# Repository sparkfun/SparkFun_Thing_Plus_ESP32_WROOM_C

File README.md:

SparkFun Thing Plus - ESP32 WROOM (USB-C)
========================================

<p align="center">

</p>

*[SparkFun Thing Plus - ESP32 WROOM (USB-C) (WRL-20168)](https://www.sparkfun.com/products/20168)*

The [SparkFun Thing Plus - ESP32 WROOM (USB-C)](https://www.sparkfun.com/products/20168) is a comprehensive development platform for [Espressif's ESP32](https://espressif.com/en/products/hardware/esp32/overview). Thanks to the onboard ESP32 WROOM module, the SparkFun Thing Plus features 16MB of flash memory, 520kB of internal SRAM, an integrated 802.11 BGN WiFi transceiver and dual-mode Bluetooth capabilities, a JST connector to plug in a LiPo battery, a Qwiic connector, and 21 I/O pins. Add to that a rich set of peripherals ranging from capacitive touch sensors, Hall sensors, SD card interface, Ethernet, high-speed SPIs, UARTs, I2S, and I2C.

We took all the good from the original [ESP32 Thing Plus](https://www.sparkfun.com/products/15663) and sprinkled on some more. We upgraded to a USB-C connector that provides up to 2A of power, added a fuel gauge IC that will make sure you know your battery levels, included a NeoPixel (WS2812C) RGB LED is the perfect multi-status indicator, and threw a microSD connector on the back! Oh, and the new taller reset and boot buttons are **so** much easier to push! We even dedicated a voltage regulator to the Qwiic connector, which enables software power control to the Qwiic bus - great for low power logging!

Repository Contents
-------------------

* **[/docs](/docs/)** - Online documentation files
    * [board_files](/docs/board_files/) - Files for the product design
        * [Eagle design files](/docs/board_files/eagle_files.zip) (.zip)
        * [Schematic](/docs/board_files/schematic.pdf) (.pdf)
        * [Dimensions](/docs/board_files/dimensions.pdf) (.pdf)
        * [Graphical Datasheet](/docs/board_files/graphical_datasheet.pdf) (.pdf)
    * [component_documentation](/docs/component_documentation/) - Datasheets for hardware components
    * [graphical_datasheet](/docs/graphical_datasheet/) - Original graphical datasheet files
    * [img/hookup_guide/](/docs/img/hookup_guide/) - Images for hookup guide documentation
* **[/Firmware](/Firmware/)** - Example sketches demonstrating extra peripherals
* **[/Hardware](/Hardware/)** - Eagle design files (.brd, .sch)

Documentation
--------------
* **[Hookup Guide](https://learn.sparkfun.com/tutorials/2353)** - Hookup guide for the ESP32 Thing Plus (USB-C).
* **[Hookup Guide (mkdocs)](http://docs.sparkfun.com/SparkFun_Thing_Plus_ESP32_WROOM_C/)** - Hookup guide for the ESP32 Thing Plus (USB-C) hosted by GitHub pages.
* **[SparkFun Graphical Datasheets](https://github.com/sparkfun/Graphical_Datasheets)** -Graphical Datasheets for various SparkFun products.
    * [Graphical Datasheet - ESP32 Thing Plus (USB-C)](/docs/board_files/graphical_datasheet.pdf) (.pdf)

Product Variants
----------------
* ESP32 Thing Plus (USB-C variant)
  * [WRL-20168](https://www.sparkfun.com/products/20168)- v1.0, Initial Release
  * [SPX-18018](https://www.sparkfun.com/products/18018) - SparkX Release
* ESP32 Thing Plus
  * [WRL-17381](https://www.sparkfun.com/products/17381) (u.FL variant) - v1.0, Initial Release
  * [WRL-15663](https://www.sparkfun.com/products/15663)- v2.0, Slight hardware update that includes a 10&ohm; series resistor between VUSB and CP2102
  * [WRL-14689](https://www.sparkfun.com/products/14689)- v1.0, Initial Release

Product Versions
----------------
* [v01](https://github.com/sparkfun/SparkFun_Thing_Plus_ESP32_WROOM_C/releases/tag/v10) - Initial Release

License Information
-------------------

This product is _**open source**_! 

Please review the LICENSE.md file for license information. 

If you have any questions or concerns on licensing, please contact technical support on our [SparkFun forums](https://forum.sparkfun.com/viewforum.php?f=152).

Distributed as-is; no warranty is given.

- Your friends at SparkFun.

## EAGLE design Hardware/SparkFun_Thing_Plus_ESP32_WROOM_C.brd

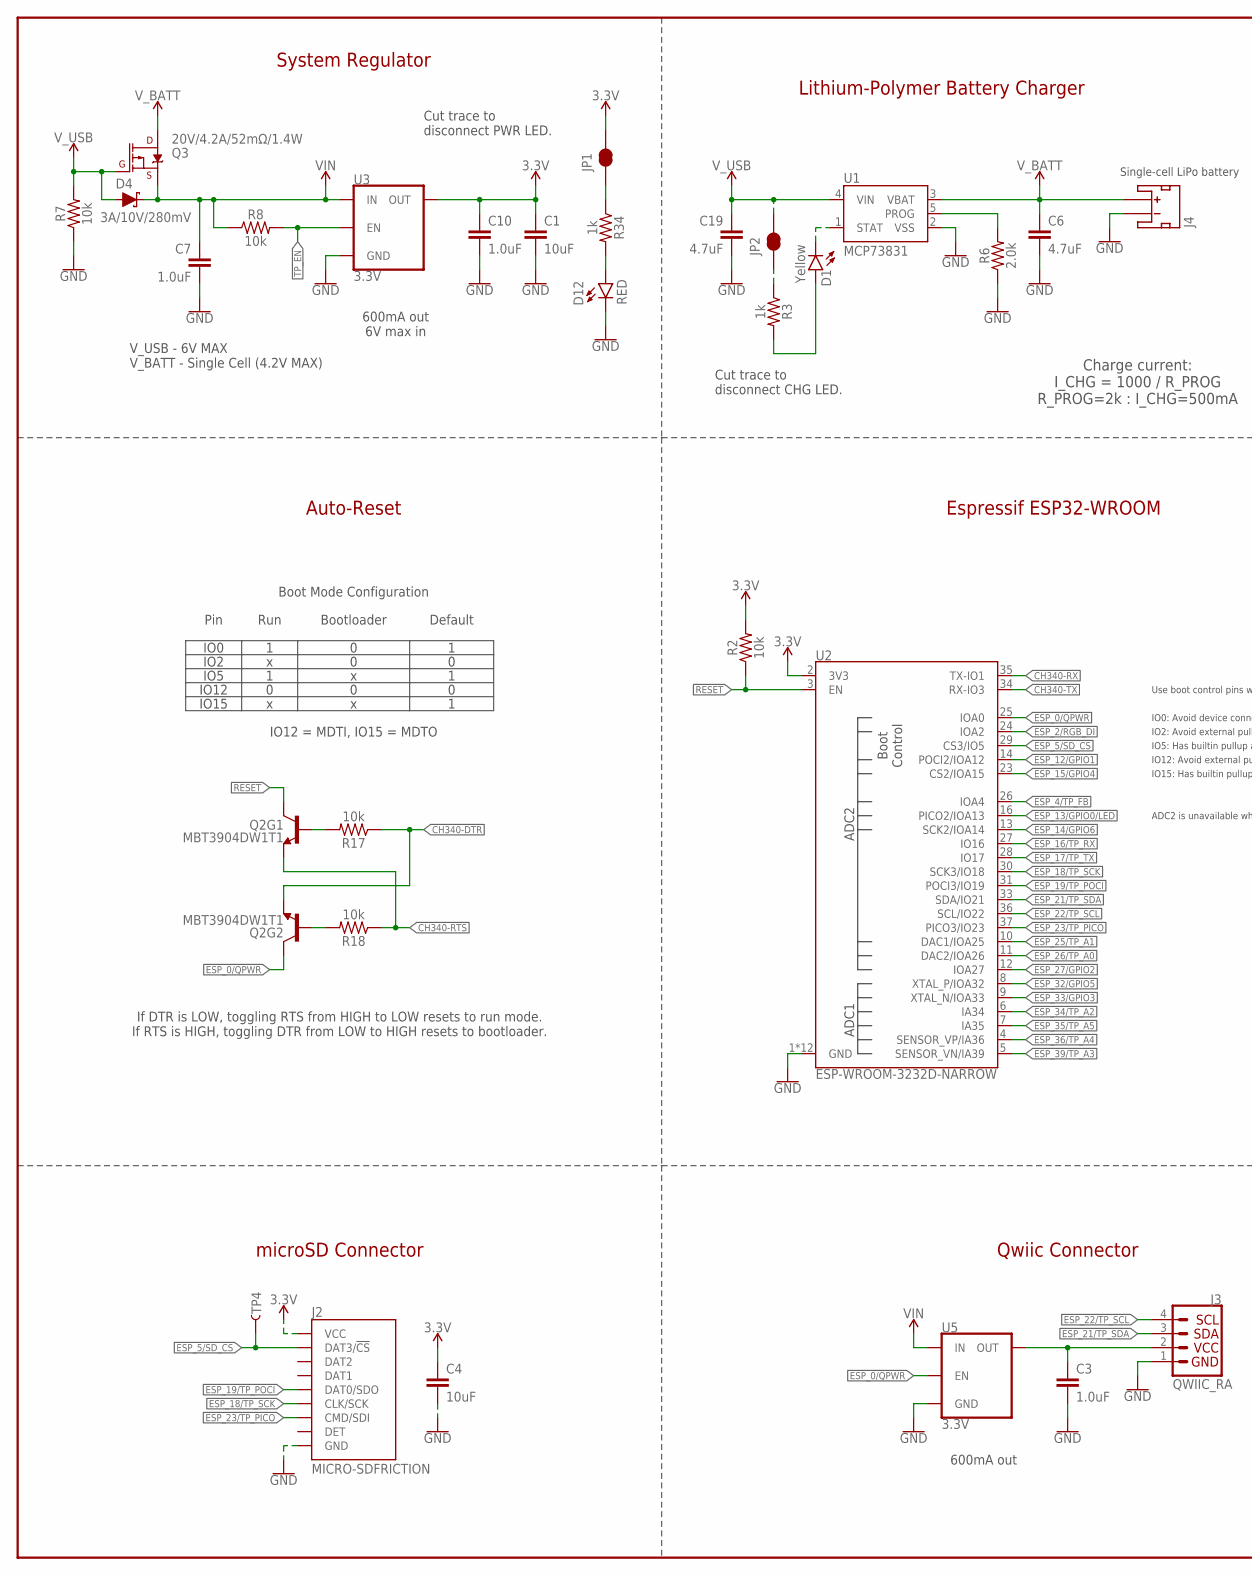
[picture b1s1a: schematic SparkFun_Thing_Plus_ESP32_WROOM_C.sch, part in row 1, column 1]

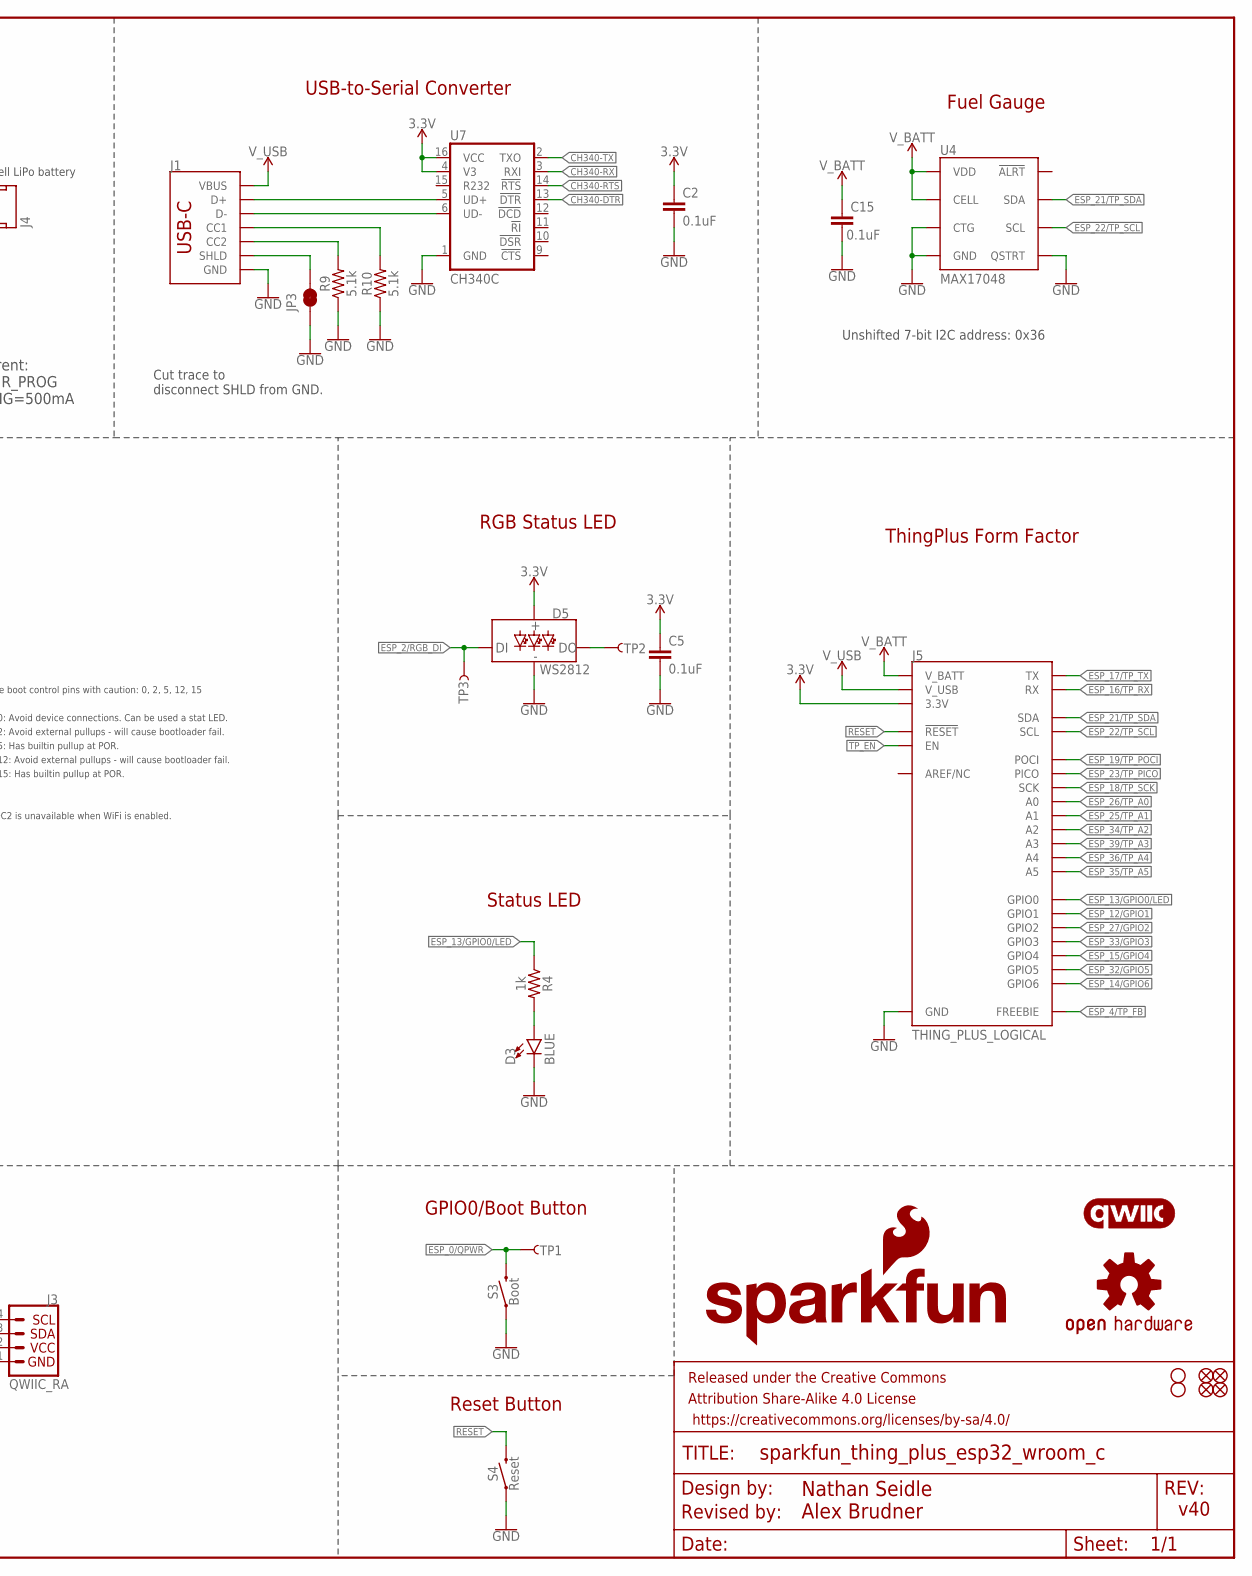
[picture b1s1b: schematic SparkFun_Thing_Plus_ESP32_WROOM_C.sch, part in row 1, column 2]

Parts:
C1, C4: 10uF; 0402-TIGHT
C2, C5, C15: 0.1uF; 0402-TIGHT
C3, C7, C10: 1.0uF; 0402-TIGHT
C6: 4.7uF; 0402-TIGHT
C19: 4.7uF; 0603
D1: Yellow; LED-0603
D3: BLUE; LED-0603
D4: 3A/10V/280mV; SOD-323
D5: WS2812; WS2812-2020
D12: RED; LED-0603
FD1, FD2, FD3, FD4: FIDUCIALUFIDUCIAL; FIDUCIAL-MICRO
FRAME1: FRAME-LEDGER; CREATIVE_COMMONS
H1, H2: STAND-OFFTIGHT; STAND-OFF-TIGHT
J1: USB_C_2-LAYER_PADS; USB-C-16P-2LAYER-PADS
J2: MICRO-SDFRICTION; MICROSD_TINY
J3: QWIIC_RA; JST04_1MM_RA
J4: JST_2MM_MALE; JST-2-SMD
J5: THING_PLUS_LOGICAL; THING_PLUS
JP1, JP2, JP3: JUMPER-SMT_2_NC_TRACE_SILK; SMT-JUMPER_2_NC_TRACE_SILK
LOGO1: SFE_LOGO_NAME_FLAME.1_INCH; SFE_LOGO_NAME_FLAME_.1
LOGO2: OSHW-LOGOMINI; OSHW-LOGO-MINI
LOGO4: QWIIC_LOGO_4MM; QWIIC_4MM
Q2: MBT3904DW1T1; SC70-6
Q3: 20V/4.2A/52mΩ/1.4W; SOT23-3
R2, R7, R8, R17, R18: 10k; 0402-TIGHT
R3, R4, R34: 1k; 0402-TIGHT
R6: 2.0k; 0603
R9, R10: 5.1k; 0402-TIGHT
S3: Boot; TACTILE_SWITCH_SMD_4.6X2.8MM
S4: Reset; TACTILE_SWITCH_SMD_4.6X2.8MM
TP1, TP2, TP3, TP4: TEST-POINT3X5; PAD.03X.05
U1: MCP73831; SOT23-5
U2: ESP-WROOM-3232D-NARROW; ESP-WROOM-32D-NARROW
U3, U5: 3.3V; SOT23-5
U4: MAX17048; DFN-8
U7: CH340C; SO016

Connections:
3.3V: C1.1, C2.1, C4.1, C5.1, C10.1, D5.VCC, J2.4 (VCC), J5.27 (3.3V), JP1.2, R2.2, U2.2 (3V3), U3.5 (OUT), U7.4 (V3), U7.16 (VCC)
!RESET!: J5.28 (!RESET), Q2.3 (C), R2.1, S4.3 (2), S4.4 (2), U2.3 (EN)
CH340-DTR: Q2.1 (E), R17.1, U7.13 (!DTR)
CH340-RTS: Q2.4 (E), R18.1, U7.14 (!RTS)
CH340-RX: U2.35 (TX-IO1), U7.3 (RXI)
CH340-TX: U2.34 (RX-IO3), U7.2 (TXO)
CHG_LED: D1.A, R3.2
D+: J1.A6 (D+), J1.B6 (D+), U7.5 (UD+)
D-: J1.A7 (D-), J1.B7 (D-), U7.6 (UD-)
DTR-10K: Q2.5 (B), R17.2
ESP_0/QPWR: Q2.6 (C), S3.3 (2), S3.4 (2), TP1.1, U2.25 (IOA0), U5.3 (EN)
ESP_2/RGB_DI: D5.DI, TP3.1, U2.24 (IOA2)
ESP_4/TP_FB: J5.13 (FREEBIE), U2.26 (IOA4)
ESP_5/SD_CS: J2.2 (DAT3/!CS!), TP4.1, U2.29 (CS3/IO5)
ESP_12/GPIO1: J5.8 (GPIO1), U2.14 (POCI2/IOA12)
ESP_13/GPIO0/LED: J5.9 (GPIO0), R4.1, U2.16 (PICO2/IOA13)
ESP_14/GPIO6: J5.3 (GPIO6), U2.13 (SCK2/IOA14)
ESP_15/GPIO4: J5.5 (GPIO4), U2.23 (CS2/IOA15)
ESP_16/TP_RX: J5.15 (RX), U2.27 (IO16)
ESP_17/TP_TX: J5.14 (TX), U2.28 (IO17)
ESP_18/TP_SCK: J2.5 (CLK/SCK), J5.18 (SCK), U2.30 (SCK3/IO18)
ESP_19/TP_POCI: J2.7 (DAT0/SDO), J5.16 (POCI), U2.31 (POCI3/IO19)
ESP_21/TP_SDA: J3.3, J5.1 (SDA), U2.33 (SDA/IO21), U4.8 (SDA)
ESP_22/TP_SCL: J3.4, J5.2 (SCL), U2.36 (SCL/IO22), U4.7 (SCL)
ESP_23/TP_PICO: J2.3 (CMD/SDI), J5.17 (PICO), U2.37 (PICO3/IO23)
ESP_25/TP_A1: J5.23 (A1), U2.10 (DAC1/IOA25)
ESP_26/TP_A0: J5.24 (A0), U2.11 (DAC2/IOA26)
ESP_27/GPIO2: J5.7 (GPIO2), U2.12 (IOA27)
ESP_32/GPIO5: J5.4 (GPIO5), U2.8 (XTAL_P/IOA32)
ESP_33/GPIO3: J5.6 (GPIO3), U2.9 (XTAL_N/IOA33)
ESP_34/TP_A2: J5.22 (A2), U2.6 (IA34)
ESP_35/TP_A5: J5.19 (A5), U2.7 (IA35)
ESP_36/TP_A4: J5.20 (A4), U2.4 (SENSOR_VP/IA36)
ESP_39/TP_A3: J5.21 (A3), U2.5 (SENSOR_VN/IA39)
GND: C1.2, C2.2, C3.2, C4.2, C5.2, C6.2, C7.2, C10.2, C15.2, C19.2, D3.C, D5.GND, D12.C, J1.GND, J1.GND2 (GND), J2.6 (GND), J2.GND1 (GND), J2.GND2 (GND), J2.GND3 (GND), J2.GND4 (GND), J2.GND5 (GND), J2.GND6 (GND), J3.1, J4.1 (-), J5.25 (GND), JP3.1, R6.1, R7.1, R9.1, R10.1, S3.1, S3.2 (1), S4.1, S4.2 (1), U1.2 (VSS), U2.1 (GND), U2.15 (GND), U2.38 (GND), U2.GND1 (GND), U2.GNDT1 (GND), U2.GNDT2 (GND), U2.GNDT3 (GND), U2.GNDT4 (GND), U2.GNDT5 (GND), U2.GNDT6 (GND), U2.GNDT7 (GND), U2.GNDT8 (GND), U3.2 (GND), U4.1 (CTG), U4.4 (GND), U4.6 (QSTRT), U4.9 (GND), U5.2 (GND), U7.1 (GND)
unnamed: JP1.1, R34.1
unnamed: D3.A, R4.2
unnamed: D5.DO, TP2.1
unnamed: JP2.1, R3.1
unnamed: J1.B5 (CC2), R9.2
unnamed: J1.A5 (CC1), R10.2
unnamed: D1.C, U1.1 (STAT)
unnamed: J1.SHLD1 (SHLD), J1.SHLD2 (SHLD), J1.SHLD3 (SHLD), J1.SHLD4 (SHLD), JP3.2
unnamed: R6.2, U1.5 (PROG)
unnamed: D12.A, R34.2
QWIIC_PWR: C3.1, J3.2, U5.5 (OUT)
RTS-10K: Q2.2 (B), R18.2
TP_EN: J5.11 (EN), R8.2, U3.3 (EN)
VIN: C7.1, D4.C, Q3.2 (S), R8.1, U3.1 (IN), U5.1 (IN)
V_BATT: C6.1, C15.1, J4.2 (+), J5.12 (V_BATT), Q3.3 (D), U1.3 (VBAT), U4.2 (CELL), U4.3 (VDD)
V_USB: C19.1, D4.A, J1.VBUS1 (VBUS), J1.VBUS2 (VBUS), J5.10 (V_USB), JP2.2, Q3.1 (G), R7.2, U1.4 (VIN)

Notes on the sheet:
USB-to-Serial Converter
Single-cell LiPo battery
Charge current: I_CHG = 1000 / R_PROG R_PROG=2k : I_CHG=500mA
System Regulator
Lithium-Polymer Battery Charger
600mA out 6V max in
Auto-Reset
Espressif ESP32-WROOM
Reset Button
ThingPlus Form Factor
v40
If DTR is LOW, toggling RTS from HIGH to LOW resets to run mode. If RTS is HIGH, toggling DTR from LOW to HIGH resets to bootloader.
Qwiic Connector
Status LED
GPIO0/Boot Button
V_USB - 6V MAX V_BATT - Single Cell (4.2V MAX)
Pin
IO0
IO2
IO12
IO15
IO5
Run
Bootloader
Default
IO12 = MDTI, IO15 = MDTO
Boot Mode Configuration
IO0: Avoid device connections. Can be used a stat LED.
ADC2 is unavailable when WiFi is enabled.
IO12: Avoid external pullups - will cause bootloader fail.
Use boot control pins with caution: 0, 2, 5, 12, 15
IO2: Avoid external pullups - will cause bootloader fail.
Fuel Gauge
600mA out
RGB Status LED
microSD Connector
IO15: Has builtin pullup at POR.
IO5: Has builtin pullup at POR.
Cut trace to disconnect CHG LED.
Cut trace to disconnect PWR LED.

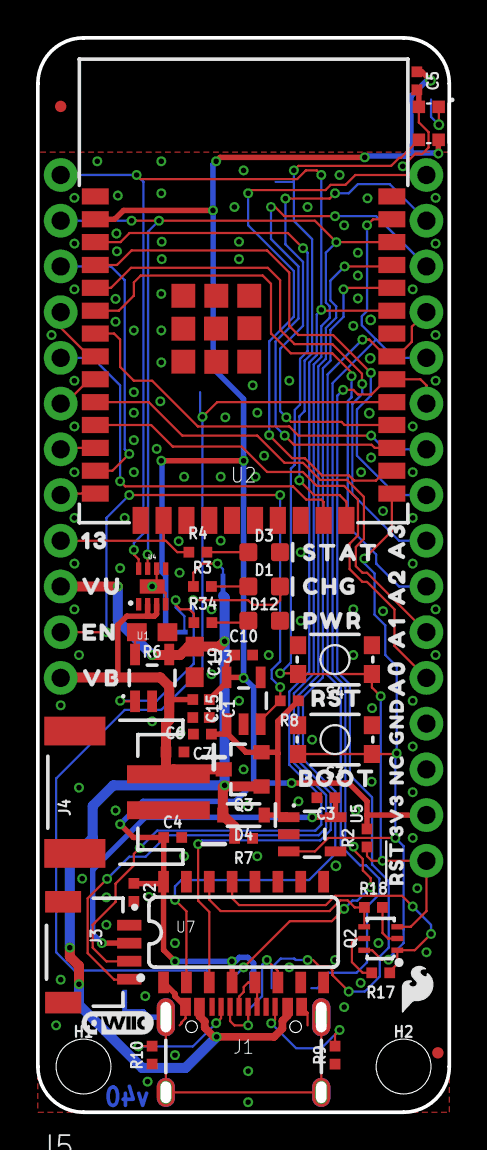
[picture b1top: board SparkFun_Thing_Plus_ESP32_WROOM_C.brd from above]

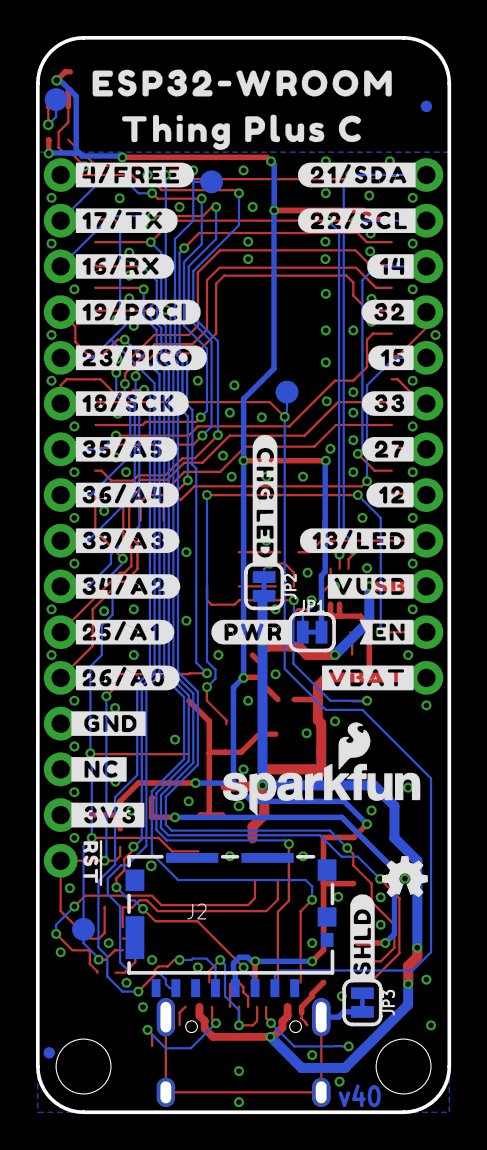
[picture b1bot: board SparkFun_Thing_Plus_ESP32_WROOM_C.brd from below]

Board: 2 copper layers, 22.9 x 59.7 mm, 110 parts (46 on the bottom side), 51 nets.

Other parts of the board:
U$1: SFE_LOGO_FLAME_STOP_.1
U$2: #23#PICO#0
U$3: #19#POCI#0
U$4: #4#FREE#0
U$5: #CHG_LED#0
U$6: ESP32#WROOM0
U$7: THING_PLUS_C0
U$8: #SHLD#0
U$9: #_GND#0
U$10: #_NC#0
U$11: #_3V3#0
U$12: SFE_LOGO_FLAME_.1
U$23: 3V30
U$24: CHG1
U$25: PWR2
U$26: STAT0
U$68: A03
U$69: A12
U$70: A21
U$71: A30
U$72: #17#TX#0
U$73: VB1
U$74: EN3
U$75: GND1
U$76: VU0
U$77: 130
U$78: BOOT0
U$79, U$109: #RST#0
U$80: RST0
U$81: #16#RX#0
U$83: #18#SCK#0
U$84: #35#A5#0
U$85: #36#A4#0
U$86: #25#A1#2
U$87: #26#A0#3
U$88: #34#A2#1
U$89: #39#A3#0
U$90: #12#4
U$91: #14#9
U$92: #15#7
U$93: #27#5
U$94: #32#8
U$95: #33#6
U$96: #EN#1
U$97: #VBAT#0
U$98: #VUSB#2
U$99: #13#LED#0
U$100: #21#SDA#1
U$101: #22#SCL#0
U$102: #PWR#0
U$107: NC0

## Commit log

2022-05-18 Pulled in files from SpX repo.
    Pulled in all the files from the SpX repo except production files and the old PDF schematic.
2022-05-19 Renamed schematics, replaced parts with sfe lib parts.
2022-05-19 All parts are now from SFE libs.
2022-05-19 Placed all new components, pinned out PTHs.
2022-05-19 End of day commit, placed uSD conn and began routing.
2022-05-20 Initial reroute complete.
2022-05-23 Completed Board update pre-DR.
2022-05-25 Completed updates post DR.
    Schematic:
    Change all text to vector, 8%
    Add row lines to boot mode table
    Add NC jumper on USB-C shield.
    Change 0.1u cap to 10u next to uSD.
    Update uSD device to pull in newest changes to keepout.
2022-05-26 Update post DR changes.
    Minor movement edits.
2022-05-26 Increase board length to sit on 0.05" grid.
    Originally had only increased by 0.01", however was told that customers prefer 0.05" increments for designing around.
2022-05-26 Added 7-bit I2C address text.
2022-05-26 Panelized for production review.
2022-05-26 Upload temp panel for Kasey.
2022-05-26 Updated panel
2022-05-26 Cammed for ordering reds.
2022-06-29 Update BOM for cap mismatch.
    Accidentally placed C4/C5 in the wrong spot. Made the change in schematic so no board reorder is necessary.
2022-06-29 Add new sketches.
    Add test sketches.
2022-07-15 Update README.md
    Clean up description and remove TBRs
    Add documentation and product version sections
    Update links
    Still needs product image
2022-08-03 Add mkdocs files
    Initial commit for documentation with mkdocs
2022-08-03 Add documentation assets
    Component datasheets
    Images for hookup guide
    Graphical datasheet files
    Add hardware assets:
    - pdfs for board dimensions, schematic, and graphical datasheet
    - .zip of eagle files (test if compatible with documentation)
2022-08-03 Update README.md
    link asset files
    add badges for issues, docs build (test), twitter
2022-08-03 Move board files
    Links break in documentation build
    Files must be within `docs` folder
2022-08-03 Index file required
    renamed introduction to index
2022-08-03 Update product documentation
    - added missing files for documentation
    - re-index files:
    - replaced introduction with index file (required)
    - replaced resources and broke down into smaller files
    - updated files to fix most formatting issues and html breakdowns
    - hardware overview (still in progress)
2022-08-09 Update graphical datasheet
    Fix error in voltage range for ESP32 module
    Should be 3.0V - 3.6V
2022-08-09 Move header to mkdocs.yml
    Removes <H1> header from markdown files
    Adds header to nav menu from mkdocs.yml
2022-08-09 Add badges
    Add badges for
    - Docs build
    - Issues
    - PR/Contributors
    - License
    - Twitter
2022-08-09 Rename file
    Rename file to resources.md
2022-08-09 Update hardware_overview.md
    Update Arduino link - documentation changed and linked to a different page
2022-08-09 Fix macros issue
    Replace columns with tables
    Replace div well with annotations
    Replace tutorial macro with img/hyperlink
    Replace video macro with embedded video
2022-08-09 Update getting_started.md
    Make indentations consistent
2022-08-09 Update hardware_overview.md
    Fix link
    Fix table spacing
    Fix annotation
    Fix table entries
2022-08-09 Create hardware_overview-tabs_version.md
    Keep back up of hardware overview section with tabs
2022-08-11 Rename and remove images
    Removed unnecessary images
    Renamed images to make more sense
2022-08-11 Update asset links
    Update docs to use local files in the repo
2022-08-11 Update sparkfun_pages.md
    Remove link to GitHub repository... documentation already in repo
2022-08-11 Add product image
    Add default product image
2022-08-11 Update index.md
    Add link to product
2022-08-11 Update documentation
    Fix bold in italics issue (can't use stars for italics)
    Set image widths
    - 500px for outside resources (product or tutorial pages)
    - 400px for internal resources (example figures or product annotations)
    Fix image links
    - html needs full link; unlike the markdown
2022-08-11 Update contribute.md
    Fix typo
2022-08-11 Update mkdocs.yml
    Set build to branch
2022-08-16 Fix spelling and grammar
    Spell Check
    Grammar
2022-08-16 Rename Files
    Renamed resource files
2022-08-18 Update README.md
    Add product image
    Fix product description
    Link folders
2022-08-18 Update README.md
    Fix product link for image
2022-08-18 Remove Fritzing link
    Did not make a Fritzing diagram for this product
2022-08-18 Fix Header
    Move header into mkdocs.yml
2022-08-18 Update README.md
    Remove "REPLACE ME" text
    Reorganize and fix repository content links
    Remove fritzing link - none made
2022-08-18 Fix images
    Link images with relative file paths
    Centering in tables <td align="center">
2022-08-18 Update README.md
    Link GitHub pages documentation
2022-08-18 Add product video
    Embedded product video
2022-08-18 Fix badges
    Move badges into text area and not in headers
2022-08-18 Move badge
    Oops... put badge in wrong text area
2022-08-18 Fix video link
    Replace placeholder link
2022-08-19 Update index.md
    Link product image to product page
2022-11-09 Update README.md
    Repo should contain MIT license for hardware/code
    CC license is for the docs
2022-11-09 Fix typos
    Fixes spelling and grammatical errors
2022-11-09 Update mkdocs.yml
    Rename Tabs/Titles
    - Product Manual -> Hookup Guide
    - <Product Name> -> Product Description
    - Contribution/Issues -> Issues/Pull Requests
2023-02-01 Consolidate resource info
    Consolidate resource information into a single file
2023-02-01 Update mkdocs.yml
    Add comments and move page info to top
2023-02-01 consolidate product info
2023-02-01 Add hard copy
    Provides users with option to view guide as a single page
    Links generated pdf of webpage (beta)
2023-02-01 add pdf rendering
2023-02-01 Custom Admonitions
2023-02-01 Update mkdocs.yml
    Add light/dark theme button
2023-02-01 Update mkdocs.yml
    move troubleshooting tips into support tab
2023-02-01 Update mkdocs.yml
    add social icon and favicon
2023-02-01 Add new page features
2023-02-01 Enable plugins
    Add installation for plugins
2023-02-01 fix hard copy stuff
    move github issue/commit files
    update links
2023-02-01 enable all plugins
    test build
2023-02-01 disable revision date
2023-02-01 update workflow
    test enable insiders build
2023-02-01 Revert "update workflow"
    This reverts commit 8af1f0109f0fd36de005d2ef8fa513474b9bacdd.
2023-02-01 update workflow
2023-02-02 Update mkdocs.yml
    update versions
2023-02-02 Update mkdocs.yml
    Update publish action: https://squidfunk.github.io/mkdocs-material/publishing-your-site/#with-github-actions
2023-02-02 remove features
    no committers or insiders
2023-02-02 test workflow
2023-02-02 remove build
2023-02-02 test
2023-02-02 move monorepo
2023-02-02 re-enable pdf
2023-02-02 insiders
2023-02-02 enable overrides
2023-02-15 Update datasheet
    New datasheet version - removes hall effect sensor info
2023-02-15 Add README files
    Change permalink icon
2023-02-21 Update mkdocs.yml
    Fix light/dark mode annotation
2023-02-21 Use figure elements
    Switch to figure elements for images
2023-02-21 Update Qwiic Logo
    Use new Qwiic logo
2023-02-21 Update copyright info
2023-02-21 Update PDF generation
    Remove subtitle and debug
2023-02-21 Update mkdocs.yml
    Remove easter egg
2023-02-21 Update Admonitions
    Use more than just the note admonition
2023-02-21 Update Docs
    Fix grammar/typos
    Sound more friendly
2023-02-21 Update tables
2023-02-21 Markdown updates
    Convert from html to markdown
2023-02-21 Update to tabs
2023-02-21 Update graphical datasheet image
    White background to be compatible with dark theme
2023-02-21 Add readme
2023-02-22 Update mkdocs.yml
    Fix product link and re-enable plugins
2023-03-22 Rename folder
2023-03-22 Update README.md
    link to release tag
2023-03-22 Update index.md
    Update to new standard
2023-03-22 Deployed 5dcb612 with MkDocs version: 1.4.2
2023-05-12 Update MAX17048_FuelGauge.ino
    Set the right adress
2023-06-21 BUGFIX: SD Card Mount Error on Thing Plus C
2023-07-19 Swap VREG IC

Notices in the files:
README.md:
License: MIT
parts and their libraries:
SparkFun-Resistors: Licensing: Creative Commons ShareAlike 4.0 International - https://creativecommons.org/licenses/by-sa/4.0
SparkFun-Aesthetics: Released under the Creative Commons Attribution Share-Alike 4.0 License
SparkFun-Aesthetics: https://creativecommons.org/licenses/by-sa/4.0
